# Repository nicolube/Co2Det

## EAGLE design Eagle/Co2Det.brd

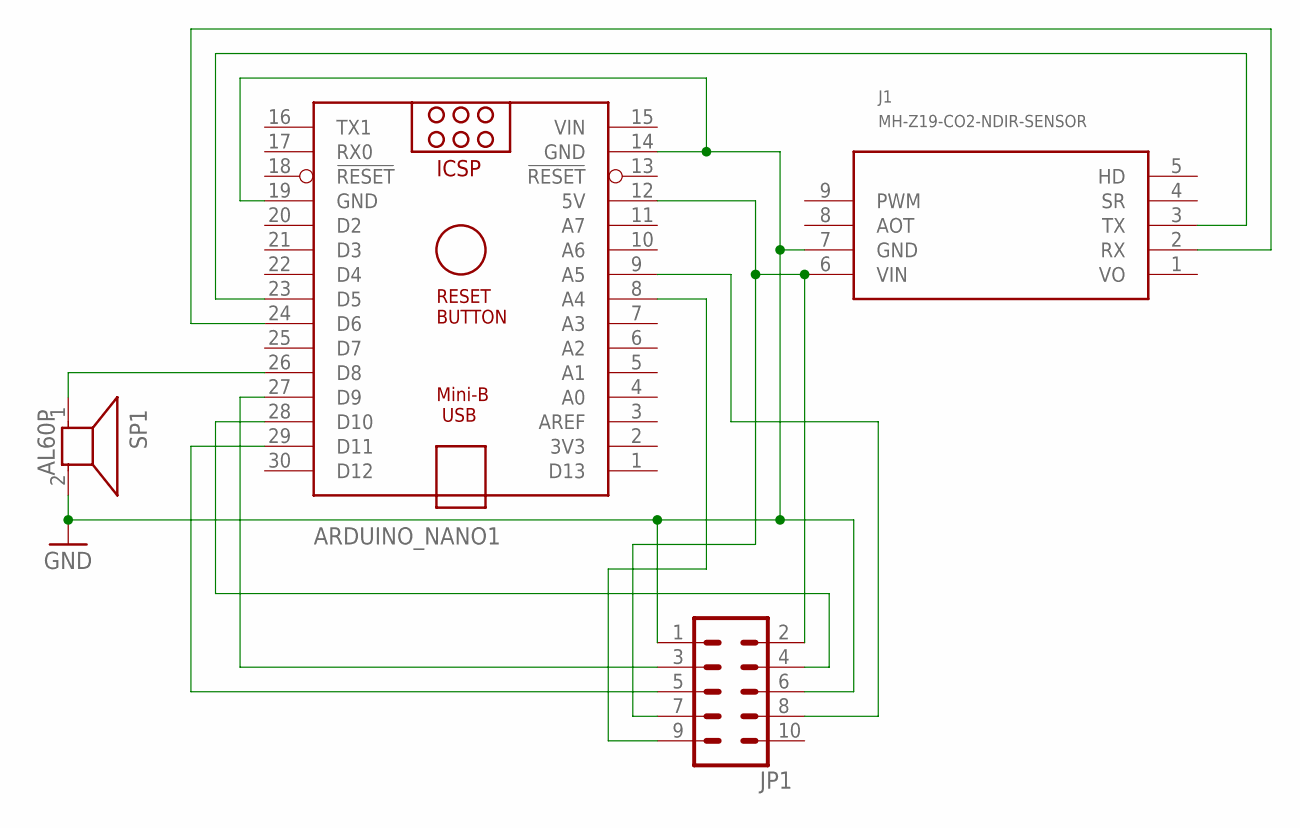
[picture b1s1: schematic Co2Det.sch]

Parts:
ARDUINO_NANO1: ARDUINO_NANO
J1: MH-Z19-CO2-NDIR-SENSOR; MH-Z19
JP1: ML10L
SP1: AL60P

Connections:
GND: ARDUINO_NANO1.14 (GND), ARDUINO_NANO1.19 (GND), J1.7 (GND), JP1.1, JP1.6, SP1.2
unnamed: ARDUINO_NANO1.12 (5V), J1.6 (VIN), JP1.2, JP1.7
unnamed: ARDUINO_NANO1.27 (D9), JP1.3
unnamed: ARDUINO_NANO1.28 (D10), JP1.4
unnamed: ARDUINO_NANO1.29 (D11), JP1.5
unnamed: ARDUINO_NANO1.23 (D5), J1.3 (TX)
unnamed: ARDUINO_NANO1.24 (D6), J1.2 (RX)
unnamed: ARDUINO_NANO1.8 (A4), JP1.9
unnamed: ARDUINO_NANO1.9 (A5), JP1.8
unnamed: ARDUINO_NANO1.26 (D8), SP1.1
VIN: ARDUINO_NANO1.15 (VIN)
VO: J1.1 (VO)

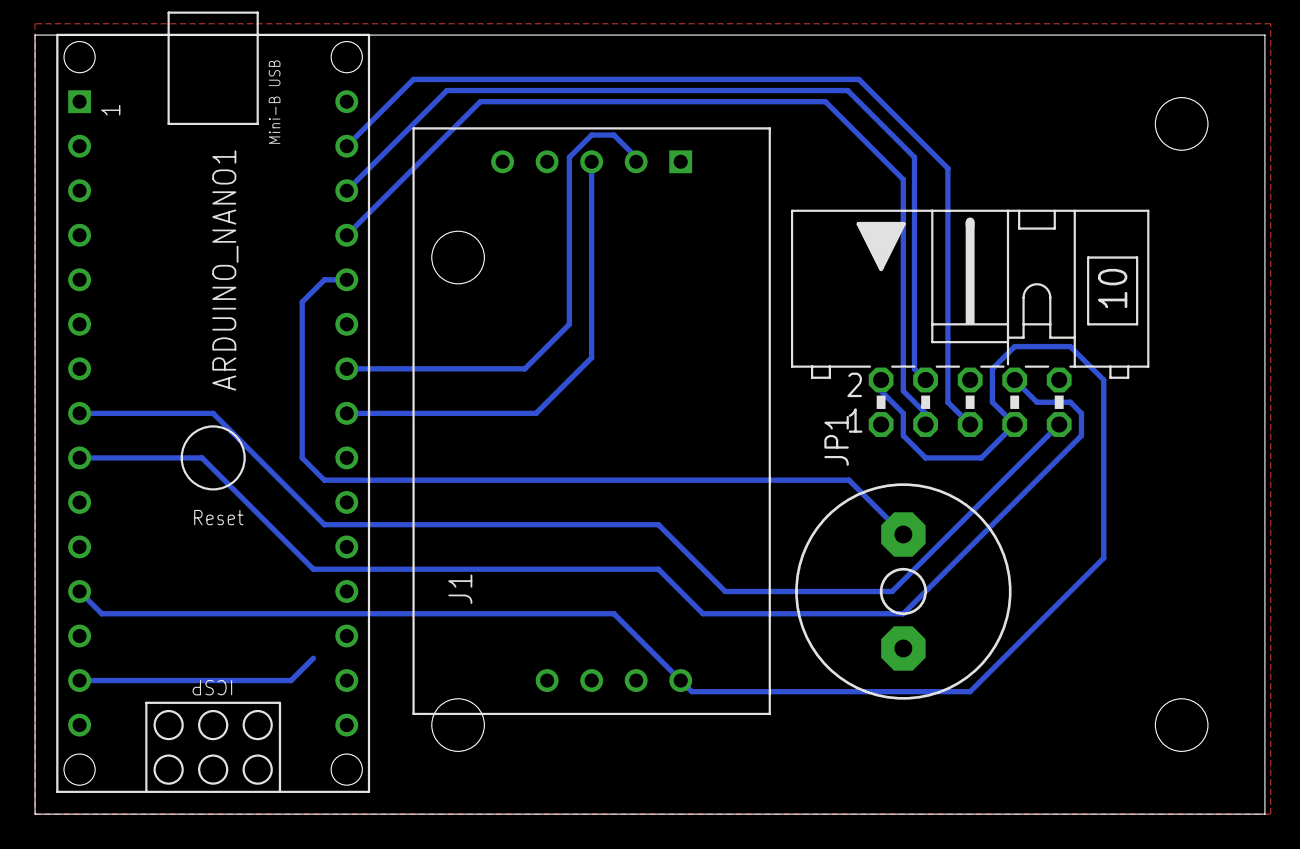
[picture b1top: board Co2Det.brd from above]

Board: 2 copper layers, 70.2 x 44.4 mm, 4 parts (0 on the bottom side), 10 nets.

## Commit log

2021-04-01 Init
2021-04-01 Add material list
2021-04-01 Added sourcecode
